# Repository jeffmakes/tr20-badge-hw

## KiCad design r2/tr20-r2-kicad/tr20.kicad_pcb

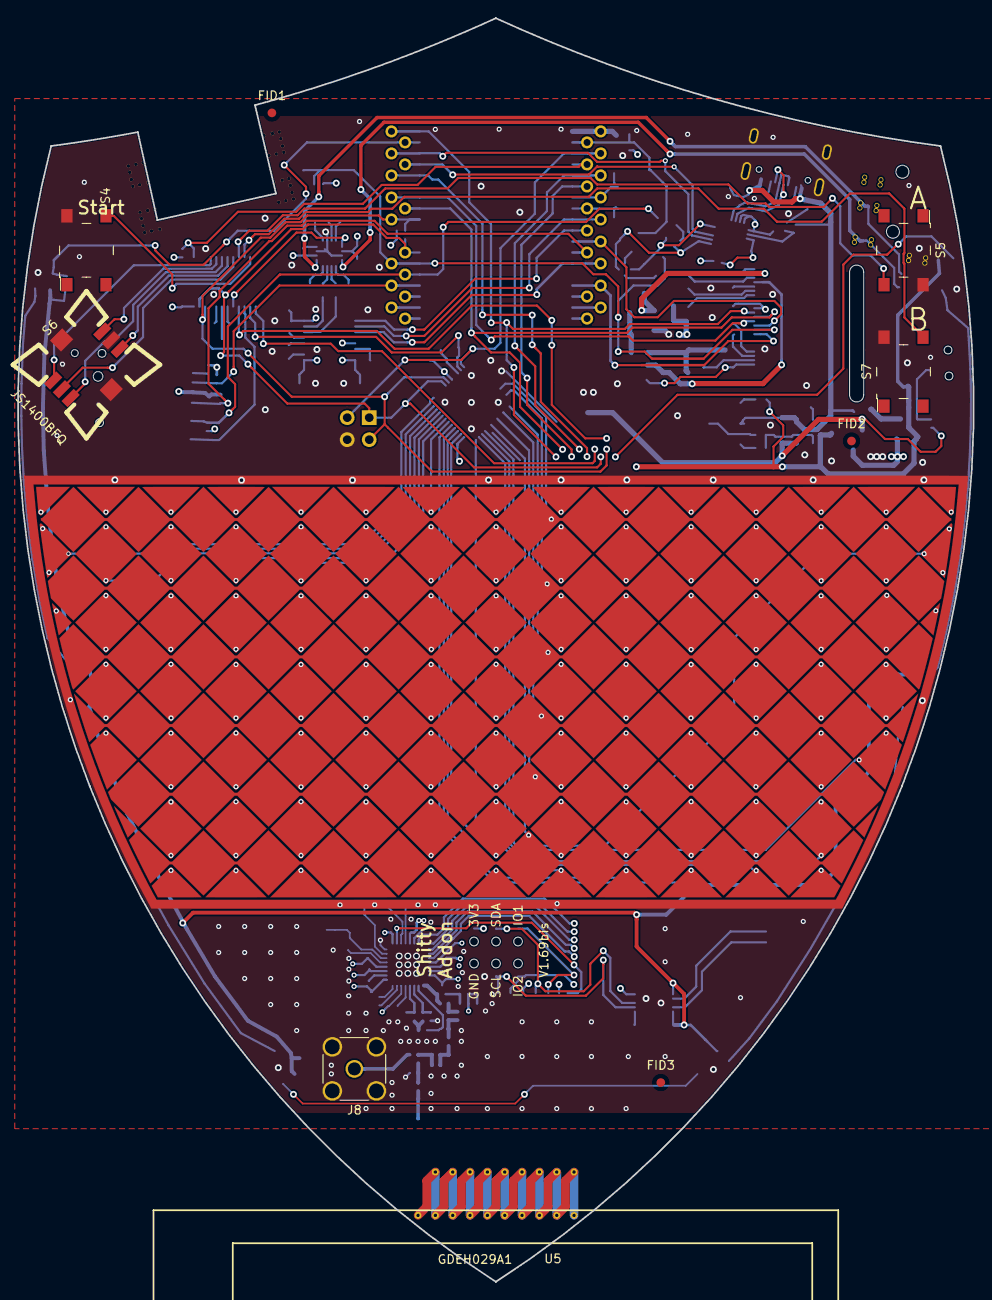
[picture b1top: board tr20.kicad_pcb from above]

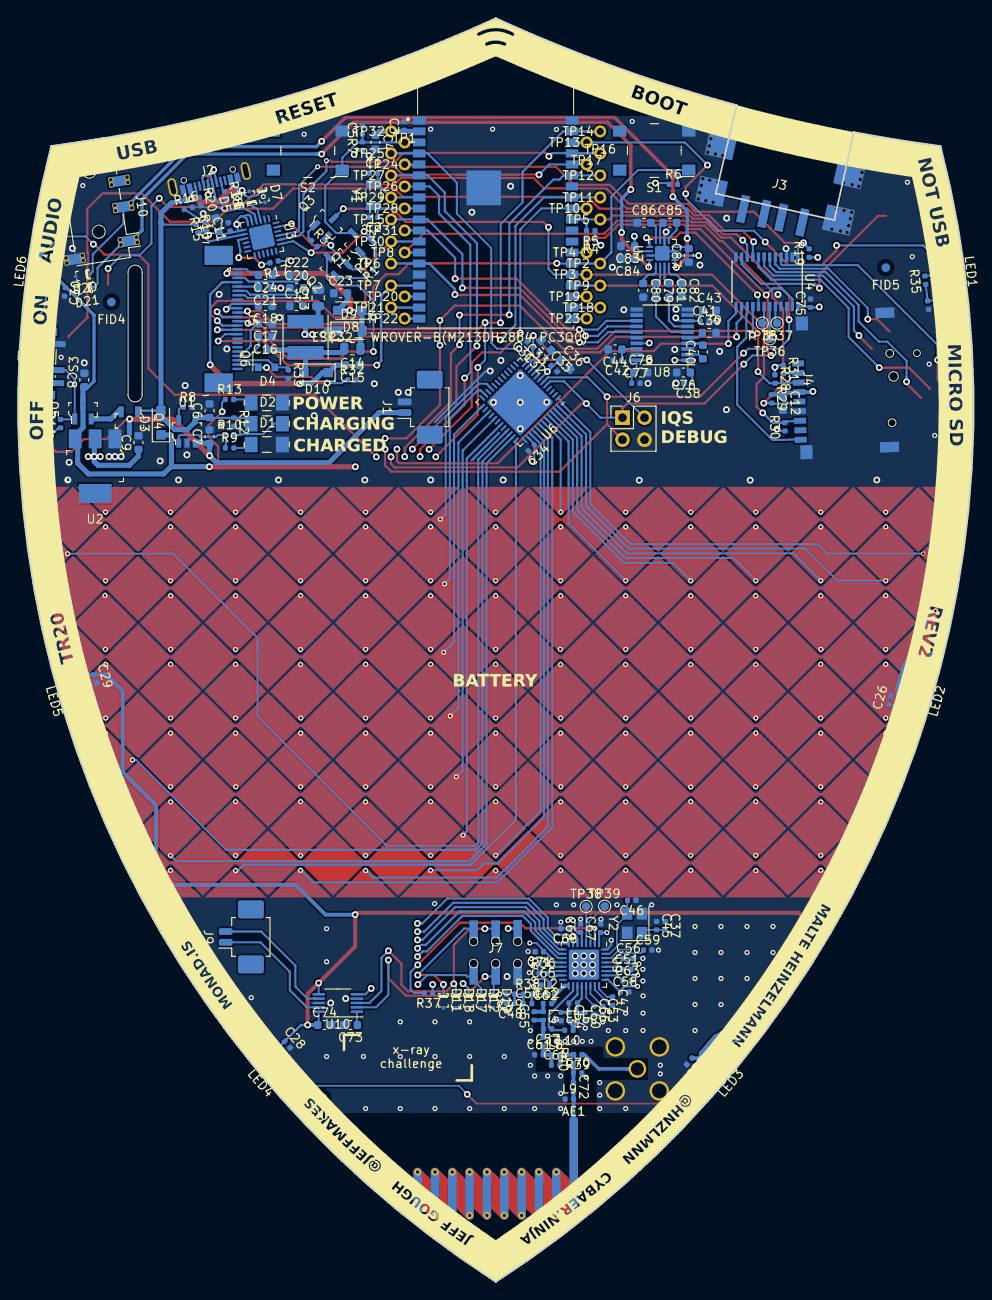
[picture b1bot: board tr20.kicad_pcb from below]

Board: 4 copper layers, 110.2 x 145.8 mm, 233 parts (223 on the bottom side), 156 nets.

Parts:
A1: ESP32- WROVER-B(M213DH2864 PC3Q0); ESP32-WROVER-I
AE1: Antenna; Antenna_TI_DN038
C1, C2, C45, C46, C52: 15pF; C_0402_1005Metric
C3, C5, C11, C25, C26, C27, C28, C29, C30, C31, C34, C38, C41, C42, C75, C77: 100nF; C_0402_1005Metric
C4, C12: 22uF; C_0603_1608Metric
C6, C7, C8, C9, C10, C15, C16, C17, C18, C19, C20, C21, C22, C23, C24, C33, C36, C39, C40, C43, C44, C73, C74, C76, C78, C79, C80, C81, C82, C83, C84, C85, C86, C87: 1uF; C_0603_1608Metric
C13, C14: 4.7uF; C_0805_2012Metric
C32, C35, C49: 100pF; C_0402_1005Metric
C37, C64, C70: DNP; C_0402_1005Metric
C47: 1.5nF; C_0402_1005Metric
C48, C66: 10nF; C_0402_1005Metric
C50: 33pF; C_0402_1005Metric
C51, C53, C56, C58, C59, C62, C63, C65, C67, C69, C71: 47nF; C_0402_1005Metric
C54, C60: 3.3pF; C_0402_1005Metric
C55, C72: 1pF; C_0402_1005Metric
C57: 2.2pF; C_0402_1005Metric
C61: 3pF; C_0402_1005Metric
C68: 220nF; C_0402_1005Metric
D1: Green; 1206
D2: Orange; 1206
D3, D8, D9, D10: SS13FL; D_SOD-123F
D4: Yellow; 1206
D5, D6, D7, D11, D12, D17, D18, D19, D20, D21: ESD5Z6.0T5G; SOD-523-numbered-pads
FID1, FID2, FID3, FID4, FID5, FID6: Fiducial; Fiducial_1mm_Mask2mm
J1, J9: 532610271; Molex_PicoBlade_53261-0271_1x02-1MP_P1.25mm_Horizontal
J2: USB-C-12; jing-usb-c-lcsc-C167321
J3: UJ2-AH-1-SMT; USB-A-short-body-in-cutout-type
J4: TF-15x15; microSD_HC_Sofng_TF-15
J5: AFC07-S24ECA-00; AFC07x24-1MP_P0.5mm_Horizontal
J6: DNP; PinHeader_2x02_P2.54mm_Vertical
J7: 2x03-socket-2.54-through-board; PinSocket_2x03_P2.54mm_Through-Board-Mating
J8: DNP; SMA_Amphenol_132291-12_Vertical
J10: PJ-320D; Jack_3.5mm_PJ320D_Horizontal_strengthening-vias
L1: 10uH 1A; L_Taiyo-Yuden_MD-5050
L2: 10nH; L_0402_1005Metric
L3, L6, L8, L9, L10: 12nH; L_0402_1005Metric
L4: 15nH; L_0402_1005Metric
L5: 7.5nH; L_0402_1005Metric
L7: 18nH; L_0402_1005Metric
LED1, LED2, LED3, LED4, LED5, LED6: SK6812; LED_SK6812MINI_PLCC4_3.5x3.5mm_P1.75mm_no_silk
Q1, Q2, Q3: MMBT3904-TP; SOT-23-3
Q4, Q5: DMG2305UX-13; SOT-23-3
Q6: SSM3K376R; SOT-23
R1, R2, R3, R6, R7, R11, R12, R14, R15, R16, R19, R28, R29, R30, R31, R32, R37: 10k; R_0402_1005Metric
R4, R5, R8, R9, R10, R13, R17, R35: 1k; R_0402_1005Metric
R18, R20: 5.1k; R_0402_1005Metric
R33: 3R; R_0402_1005Metric
R36: 56k; R_0402_1005Metric
R38: 10R; R_0402_1005Metric
R39: DNP; R_0402_1005Metric
R40: 0R; R_0402_1005Metric
S1, S2, S4, S5, S7: PTS645SM43SMTR92_LFS; Switch_Tactile_SMD_6x6mm_PTS645
S3: JS102011SAQN; SW_SPDT_PCM12
S6: JS1400BFQ; SW_JS1400BFQ-arrows
TP1, TP2, TP3, TP4, TP5, TP6, TP7, TP8, TP9, TP10, TP11, TP12, TP13, TP14, TP15, TP16, TP17, TP18, TP19, TP20, TP21, TP22, TP23, TP24, TP25, TP26, TP27, TP28, TP29, TP30, TP31, TP32: test-pad-1.4-TH
TP35, TP36, TP37, TP38, TP39: TestPoint_Pad_D1.0mm
U1: MCP73831T-2ACI_OT; SOT-753
U2: AP2114H-3_3TRG1; SOT-223
U3: CP2102N-A01-GQFN24; QFN-24-1EP_4x4mm_P0.5mm_EP2.6x2.6mm
U4: PCA9555; TSSOP-24_4.4x7.8mm_P0.65mm
U5: GDEH029A1
U6: IQS550; QFN-48-1EP_7x7mm_P0.5mm_EP5.45x5.45mm
U7: PAM8908; QFN-16-1EP_3x3mm_P0.5mm_EP1.7x1.7mm
U8: PCM5100A; TSSOP-20_4.4x6.5mm_P0.65mm
U9: CC1200; QFN-32-1EP_5x5mm_P0.5mm_EP3.45x3.45mm
U10: DRV2605LDGS; VSSOP-10_3x3mm_P0.5mm
XY1: tr20_touch_array; Touch_Array_TR20
Y1: 32.768kHz; Crystal_SMD_3215-2Pin_3.2x1.5mm
Y2: 40Mhz; Crystal_SMD_3225-4Pin_3.2x2.5mm

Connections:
+3V3: A1.2, C3.1, C4.1, C9.1, C10.1, C11.1, C12.1, C13.1, C18.2, C34.1, C35.1, C36.1, C38.1, C41.1, C43.1, C48.1, C49.1, C50.1, C51.1, C53.1, C56.1, C58.1, C62.1, C65.1, C67.1, C69.1, C71.1, C75.1, C76.1, C77.1, C78.1, C83.1, C84.1, D17.1, J4.4, J5.9, J5.10, J7.1, L1.1, R4.1, R5.1, R6.1, R7.1, R17.1, R19.1, R28.1, R29.1, R30.1, R31.1, R37.1, R38.1, TP32.1, U2.2, U3.5, U3.6, U3.7, U4.24, U6.7, U6.38, U7.6, U7.14, U8.1, U8.8, U8.17, U8.20, U9.1, U9.5, U9.12, U9.13, U9.15, U9.22, U9.25, U9.27, U9.28, U10.5
+BATT: C7.1, J1.1, Q4.3, R11.1, U1.3
+VSW: C8.1, C25.1, C26.1, C27.1, C28.1, C29.1, C30.1, C74.1, D3.1, LED1.3, LED2.3, LED3.3, LED4.3, LED5.3, LED6.3, Q5.3, R13.1, R35.1, U2.3, U10.6, U10.10
/32K_XN: A1.9, C2.1, TP28.1, Y1.2
/32K_XP: A1.8, C1.2, TP29.1, Y1.1
/AMP_EN: U4.17, U7.13
/BTN_INT: A1.5, R19.2, TP24.1, U4.1
/CC_INT: A1.6, TP27.1, U9.10
/CC_RESET: R37.2, U4.13, U9.2
/DISP_BUSY: A1.16, J5.16, TP7.1
/DTR: Q2.2, Q3.2, R1.2, U3.23
/EN: A1.3, C5.1, Q1.3, R7.2, S2.1, TP1.1
/I2S_SCK: A1.11, TP31.1, U8.13
/I2S_SD: A1.10, TP15.1, U8.14
/I2S_WS: A1.14, TP6.1, U8.15
/IO0: A1.25, J5.15, Q2.3, R6.2, S1.1, TP2.1
/IQ_RDY: A1.4, J6.2, TP25.1, U6.11
/IQ_RESET: C31.1, U4.14, U6.10
/LED_DIN: A1.36, LED1.2, R35.2, TP13.1
/LED_DOUT: D11.1, J7.5, LED6.4
/MISO: A1.7, TP26.1, U9.9
/MOSI: A1.37, J5.11, TP14.1, U9.7
/P1_5: TP35.1, U4.18
/P1_6: TP36.1, U4.19
/P1_7: TP37.1, U4.20
/RTS: Q1.2, R2.2, R3.2, U3.19
/RXD0: A1.34, TP17.1, U3.21
/SAO_GPIO2: D12.1, J7.6, U4.16
/SCK: A1.30, J5.12, TP10.1, U9.8
/SCL: A1.29, D19.1, J6.3, J7.4, R5.2, TP5.1, U4.22, U6.6, U10.2
/SDA: A1.26, D18.1, J6.1, J7.3, R4.2, TP4.1, U4.23, U6.5, U10.3
/SD_CLK: A1.13, J4.5, R29.2, TP8.1
/SD_CMD: A1.23, J4.3, R28.2, TP9.1
/SD_DAT0: A1.24, J4.7, Q3.3, R30.2, TP3.1
/SD_DETECT: J4.CD, U4.15
/TXD0: A1.35, TP16.1, U3.20
/_reserved6: A1.20, TP23.1
/_reserved7: A1.21, TP18.1
/_reserved8: A1.22, TP19.1
/_reserved9: A1.17, TP20.1
/_reserved10: A1.18, TP21.1
/_reserved11: A1.19, TP22.1
/audio/DAC_OUTL: C79.2, U8.6
/audio/DAC_OUTR: C81.2, U8.7
/audio/LDO0: C42.1, C44.1, U8.18
/audio/OUTL: D21.1, J10.T, U7.16
/audio/OUTR: D20.1, J10.R1, U7.5
/display/GDR: J5.23, Q6.1, R32.1
/display/PREVGH: C15.2, D10.1, J5.4
/display/PREVGL: C23.2, D8.2, J5.2
/display/RESE: J5.22, Q6.2, R33.1
/display/d_VCOM: C24.2, J5.1
/display/d_VDD: C19.2, J5.7
/display/d_VGH: C17.2, J5.20
/display/d_VGL: C16.2, J5.21
/display/d_VPP: C20.2, J5.6
/display/d_VSH: C21.2, J5.5
/display/d_VSL: C22.2, J5.3
/io_expander/BTN_A: S5.4, U4.9
/io_expander/BTN_B: S7.4, U4.10
/io_expander/BTN_START: S4.4, U4.11
/io_expander/JOY_A: S6.1, U4.4
/io_expander/JOY_B: S6.4, U4.5
/io_expander/JOY_C: S6.3, U4.6
/io_expander/JOY_D: S6.6, U4.7
/io_expander/JOY_PUSH: S6.2, U4.8
/power/~PWR_EN~: Q5.1, R11.2, S3.2
/touchpad/Rx4A: U6.21, XY1.RX0
/touchpad/Rx5A: U6.23, XY1.RX1
/touchpad/Rx6A: U6.25, XY1.RX2
/touchpad/Rx7A: U6.27, XY1.RX3
/touchpad/Rx8A: U6.29, XY1.RX4
/touchpad/Rx9A: U6.31, XY1.RX5
/touchpad/Tx0: U6.33, XY1.TX14
/touchpad/Tx1: U6.34, XY1.TX13
/touchpad/Tx2: U6.35, XY1.TX12
/touchpad/Tx3: U6.36, XY1.TX11
/touchpad/Tx4: U6.39, XY1.TX7
/touchpad/Tx5: U6.40, XY1.TX8
/touchpad/Tx6: U6.41, XY1.TX9
/touchpad/Tx7: U6.42, XY1.TX10
/touchpad/Tx8: U6.43, XY1.TX6
/touchpad/Tx9: U6.44, XY1.TX5
/touchpad/Tx10: U6.45, XY1.TX4
/touchpad/Tx11: U6.46, XY1.TX3
/touchpad/Tx12: U6.47, XY1.TX2
/touchpad/Tx13: U6.48, XY1.TX1
/touchpad/Tx14: U6.1, XY1.TX0
/usb/USB_DN: D5.1, J2.A7, J2.B7, U3.4
/usb/USB_DP: D6.1, J2.A6, J2.B6, U3.3
/~CC_CS~: A1.33, TP12.1, U9.11
/~DC~: A1.12, J5.14, TP30.1
/~DISP_CS~: A1.31, J5.13, TP11.1
GND: A1.1, A1.15, A1.38, A1.39, C1.1, C2.2, C3.2, C4.2, C5.2, C6.2, C7.2, C8.2, C9.2, C10.2, C11.2, C12.2, C13.2, C15.1, C16.1, C17.1, C18.1, C19.1, C20.1, C21.1, C22.1, C23.1, C24.1, C25.2, C26.2, C27.2, C28.2, C29.2, C30.2, C31.2, C32.2, C33.2, C34.2, C35.2, C36.2, C37.1, C38.2, C39.2, C41.2, C42.2, C43.2, C44.2, C45.1, C46.1, C48.2, C49.2, C51.2, C53.2, C56.2, C58.2, C59.2, C60.2, C61.1, C62.2, C63.2, C65.2, C66.2, C67.2, C68.2, C69.2, C70.2, C71.2, C73.2, C74.2, C75.2, C76.2, C77.2, C78.2, C80.2, C82.2, C83.2, C84.2, C86.1, C87.1, D1.2, D4.2, D5.2, D6.2, D7.2, D9.1, D11.2, D12.2, D17.2, D18.2, D19.2, D20.2, D21.2, J1.2, J2.A1, J2.B1, J2.SH, J3.5, J4.6, J4.G, J5.8, J5.17, J6.4, J7.2, J8.2, J10.S, L3.2, L9.1, LED1.1, LED2.1, LED3.1, LED4.1, LED5.1, LED6.1, R8.2, R12.2, R16.2, R18.2, R20.2, R32.2, R33.2, R36.1, S1.3, S2.3, S3.1, S4.2, S5.2, S6.5, S6.SH1, S6.SH2, S7.2, U1.2, U2.1, U3.2, U3.25, U4.2, U4.3, U4.12, U4.21, U6.8, U6.37, U6.49, U7.7, U7.10, U7.15, U7.17, U8.3, U8.9, U8.10, U8.11, U8.12, U8.16, U8.19, U9.32, U9.33, U10.4, U10.8, XY1.GND, Y2.2, Y2.4
unnamed: AE1.1, C72.2, L9.2
unnamed: C14.1, D8.1, D9.2
unnamed: C14.2, D10.2, L1.2, Q6.3
unnamed: C32.1, C33.1, U6.9
unnamed: C37.2, C45.2, U9.30, Y2.1
unnamed: C39.1, U8.5
unnamed: C40.1, U8.2
unnamed: C40.2, U8.4
unnamed: C46.2, U9.31, Y2.3
unnamed: C47.1, U9.24
unnamed: C47.2, U9.23
unnamed: C50.2, L2.1, R38.2
unnamed: C52.1, C55.2, L5.1
unnamed: C52.2, L2.2, U9.17
unnamed: C54.1, L3.1, L4.2, U9.19
unnamed: C54.2, L6.2, L10.1
unnamed: C55.1, C57.2, L5.2, L7.1
unnamed: C57.1, L10.2, U9.18
unnamed: C59.1, U9.29
unnamed: C60.1, L4.1, L6.1, U9.20
unnamed: C61.2, C64.1, L7.2, L8.1
unnamed: C63.1, U9.26
unnamed: C64.2, L8.2, R39.2, R40.2
unnamed: C66.1, U9.21
unnamed: C68.1, U9.6
unnamed: C70.1, C72.1, R40.1
unnamed: C73.1, U10.1
unnamed: C79.1, U7.2
unnamed: C80.1, U7.1
unnamed: C81.1, U7.3
unnamed: C82.1, U7.4
unnamed: C85.1, U7.11
unnamed: C85.2, U7.9
unnamed: C86.2, U7.12
unnamed: C87.2, U7.8
unnamed: D1.1, R9.2
unnamed: D2.2, R10.2
unnamed: D4.1, R13.2
unnamed: J2.A5, R18.1
unnamed: J2.B5, R20.1
unnamed: J4.2, R31.2
unnamed: J8.1, R39.1
unnamed: J9.1, U10.9
unnamed: J9.2, U10.7
unnamed: LED1.4, LED2.2
unnamed: LED2.4, LED3.2
unnamed: LED3.4, LED4.2
unnamed: LED4.4, LED5.2
unnamed: LED5.4, LED6.2
unnamed: Q1.1, R1.1
unnamed: Q2.1, R2.1
unnamed: Q3.1, R3.1
unnamed: Q4.2, Q5.2
unnamed: R8.1, U1.5
unnamed: R9.1, R10.1, U1.1
unnamed: R14.2, R15.1, U3.8
unnamed: R15.2, R16.1
unnamed: R17.2, U3.9
unnamed: R36.2, U9.14
unnamed: TP38.1, U9.4
unnamed: TP39.1, U9.3
VBUS: C6.1, D2.1, D3.2, D7.1, J2.A4, J2.B4, Q4.1, R12.1, R14.1, U1.4

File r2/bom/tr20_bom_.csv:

References,Quantity Per PCB,Value,Rating,Manufacturer,MPN,Description,Footprint
A1,1,ESP32-WROVER,,,,,ESP32-WROVER-I
C47,1,1.5nF,,,,Unpolarized capacitor,C_0402_1005Metric
C3 C5 C11 C25 C26 C27 C28 C29 C30 C31 C34 C38 C41 C42 C75 C77,16,100nF,,,,Unpolarized capacitor,C_0402_1005Metric
C32 C35 C49,3,100pF,,,,Unpolarized capacitor,C_0402_1005Metric
C48 C66,2,10nF,,,,Unpolarized capacitor,C_0402_1005Metric
C1 C2 C45 C46 C52,5,15pF,,,,Unpolarized capacitor,C_0402_1005Metric
C55 C72,2,1pF,,,,Unpolarized capacitor,C_0402_1005Metric
C6 C7 C8 C9 C10 C15 C16 C17 C18 C19 C20 C21 C22 C23 C24 C33 C36 C39 C40 C43 C44 C73 C74 C76 C78 C79 C80 C81 C82 C83 C84 C85 C86 C87,34,1uF,50V,,,Unpolarized capacitor,C_0603_1608Metric
C57,1,2.2pF,,,,Unpolarized capacitor,C_0402_1005Metric
C68,1,220nF,,,,Unpolarized capacitor,C_0402_1005Metric
C4 C12,2,22uF,,,,Unpolarized capacitor,C_0603_1608Metric
C54 C60,2,3.3pF,,,,Unpolarized capacitor,C_0402_1005Metric
C50,1,33pF,,,,Unpolarized capacitor,C_0402_1005Metric
C61,1,3pF,,,,Unpolarized capacitor,C_0402_1005Metric
C13 C14,2,4.7uF,,,,Unpolarized capacitor,C_0805_2012Metric
C51 C53 C56 C58 C59 C62 C63 C65 C67 C69 C71,11,47nF,,,,Unpolarized capacitor,C_0402_1005Metric
D5 D6 D7 D11 D12 D17 D18 D19 D20 D21,10, ESD5Z6.0T5G,,,ESD5Z5.0VC,Bidirectional transient-voltage-suppression diode,SOD-523-numbered-pads
D1,1,Green,,Lite-On Inc.,LTST-C150KGKT,LED GREEN CLEAR 1206 SMD,1206
D2,1,Orange,,Lite-On Inc.,LTST-C150KSKT,LED YELLOW CLEAR 1206 SMD,1206
D3 D8 D9 D10,4,SS13FL,,,,Schottky diode,D_SOD-123F
D4,1,Yellow,,Lite-On Inc.,LTST-C150KSKT,LED YELLOW CLEAR 1206 SMD,1206
J7,1,2x03-socket-2.54-through-board,,,,"Generic connector, double row, 02x03, odd/even pin numbering scheme (row 1 odd numbers, row 2 even numbers), script generated (kicad-library-utils/schlib/autogen/connector/)",PinSocket_2x03_P2.54mm_Through-Board-Mating
J1 J9,2,532610271,,,,"Generic connector, single row, 01x02, script generated (kicad-library-utils/schlib/autogen/connector/)",Molex_PicoBlade_53261-0271_1x02-1MP_P1.25mm_Horizontal
J5,1,AFC07-S24ECA-00,,,,"Generic connector, single row, 01x24, script generated (kicad-library-utils/schlib/autogen/connector/)",AFC07x24-1MP_P0.5mm_Horizontal
J10,1,PJ-320D,,,,"Audio Jack, 4 Poles (TRRS)",Jack_3.5mm_PJ320D_Horizontal
J4,1,TF-15x15,,,,,microSD_HC_Sofng_TF-15
J3,1,UJ2-AH-1-SMT,,,,USB Type A connector,USB-A-short-body
J2,1,USB-C-12,,,,,jing-usb-c-lcsc-C167321
L2,1,10nH,,,,Inductor,L_0402_1005Metric
L1,1,10uH 1A,,,NRS4018T100M,Inductor,L_Taiyo-Yuden_MD-5050
L3 L6 L8 L9 L10,5,12nH,,,,Inductor,L_0402_1005Metric
L4,1,15nH,,,,Inductor,L_0402_1005Metric
L7,1,18nH,,,,Inductor,L_0402_1005Metric
L5,1,7.5nH,,,,Inductor,L_0402_1005Metric
LED1 LED2 LED3 LED4 LED5 LED6,6,SK6812,,,,RGB LED with integrated controller,LED_SK6812MINI_PLCC4_3.5x3.5mm_P1.75mm_no_silk
Q4 Q5,2,DMG2305UX-13,,Diodes Incorporated,DMG2305UX-13,MOSFET P-CH 20V 4.2A SOT23,SOT-23-3
Q1 Q2 Q3,3,MMBT3904-TP,,Micro Commercial Co,MMBT3904-TP,TRANS NPN 40V 0.2A SOT23,SOT-23-3
Q6,1,SSM3K376R,,,,"0.115A Id, 60V Vds, N-Channel MOSFET, SOT-23",SOT-23
R40,1,0R,,,,Resistor,R_0402_1005Metric
R38,1,10R,,,,Resistor,R_0402_1005Metric
R1 R2 R3 R6 R7 R11 R12 R14 R15 R16 R19 R28 R29 R30 R31 R32 R37,17,10k,,,,Resistor,R_0402_1005Metric
R4 R5 R8 R9 R10 R13 R17 R35,8,1k,,,,Resistor,R_0402_1005Metric
R33,1,3R,,,,Resistor,R_0402_1005Metric
R18 R20,2,5.1k,,,,Resistor,R_0402_1005Metric
R36,1,56k,,,,Resistor,R_0402_1005Metric
S6,1, JS1400BFQ,,,,,SW_JS1400BFQ-arrows
S3,1,JS102011SAQN,,,,,SW_SPDT_PCM12
S1 S2 S4 S5 S7,5,PTS645SM43SMTR92_LFS,,C&K,PTS645SM43SMTR92 LFS,SWITCH TACTILE SPST-NO 0.05A 12V,Switch_Tactile_SMD_6x6mm_PTS645
U2,1,AP2114H-3_3TRG1,,Diodes Incorporated,AP2114H-3.3TRG1,IC REG LINEAR 3.3V 1A SOT223,SOT-223
U9,1,CC1200,,,,"Low-Power, High-Performance RF Transceiver, QFN-32",QFN-32-1EP_5x5mm_P0.5mm_EP3.45x3.45mm
U3,1,CP2102N-A01-GQFN24,,,,"USB to UART master bridge, QFN-24",QFN-24-1EP_4x4mm_P0.5mm_EP2.6x2.6mm
U10,1,DRV2605LDGS,,,,,VSSOP-10_3x3mm_P0.5mm
U5,1,GDEH029A1,,,,,GDEH029A1
U6,1,IQS550,,,,,QFN-48-1EP_7x7mm_P0.5mm_EP5.45x5.45mm
U1,1,MCP73831T-2ACI_OT,,Microchip Technology,MCP73831T-2ACI/OT,IC CONTROLLR LI-ION 4.2V SOT23-5,SOT-753
U7,1,PAM8908,,,,,QFN-16-1EP_3x3mm_P0.5mm_EP1.7x1.7mm
U4,1,PCA9555,,,,,TSSOP-24_4.4x7.8mm_P0.65mm
U8,1,PCM5100A,,,,"2VRMS DirectPath, 100dB Audio Stereo DAC with 32-bit, 384kHz PCM Interface, TSSOP-20",TSSOP-20_4.4x6.5mm_P0.65mm
Y1,1,32.768kHz,,,SSP-T7-F,Two pin crystal,Crystal_SMD_3215-2Pin_3.2x1.5mm
Y2,1,40Mhz,,,,"Four pin crystal, GND on pins 2 and 4",Crystal_SMD_3225-4Pin_3.2x2.5mm





Component Groups:,64
Component Count:,188
Fitted Components:,182
Number of PCBs:,1
Total components:,182
Schematic Version:,
Schematic Date:,
PCB Variant:,"""default"""
BoM Date:,Thu 19 Dec 2019 18:07:54 CST
Schematic Source:,/home/jeff/projects/2019/tr20-badge/repos/tr20-badge-hw/r2/tr20/tr20.sch
KiCad Version:,Eeschema 5.99.0-unknown-r17145-8bd2765f
